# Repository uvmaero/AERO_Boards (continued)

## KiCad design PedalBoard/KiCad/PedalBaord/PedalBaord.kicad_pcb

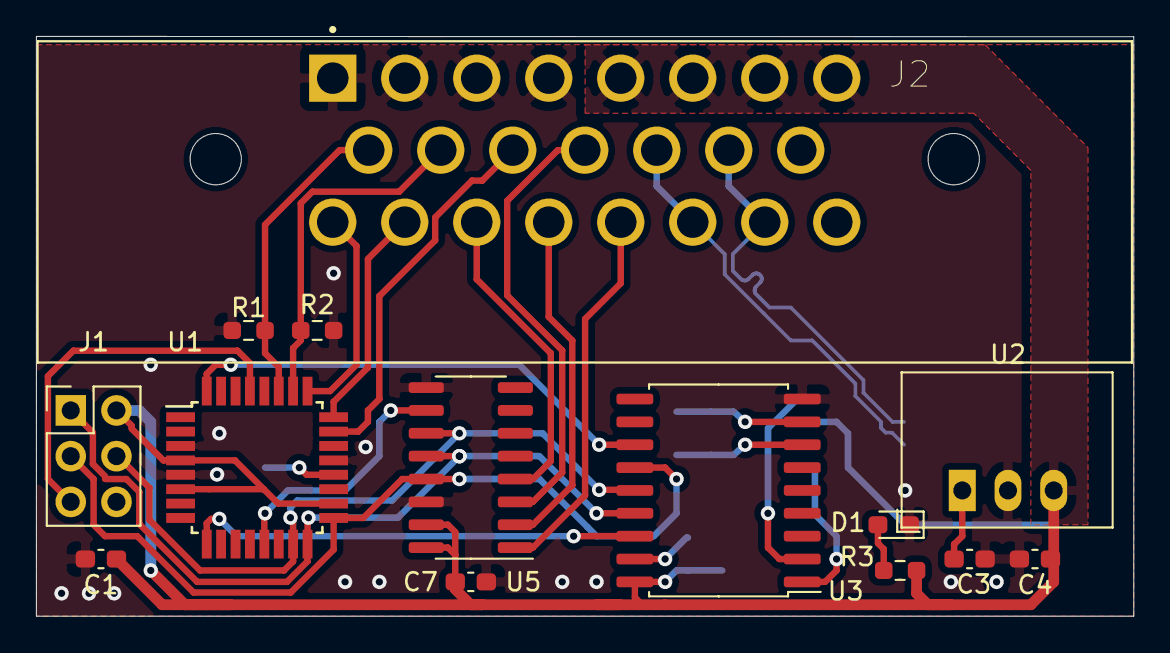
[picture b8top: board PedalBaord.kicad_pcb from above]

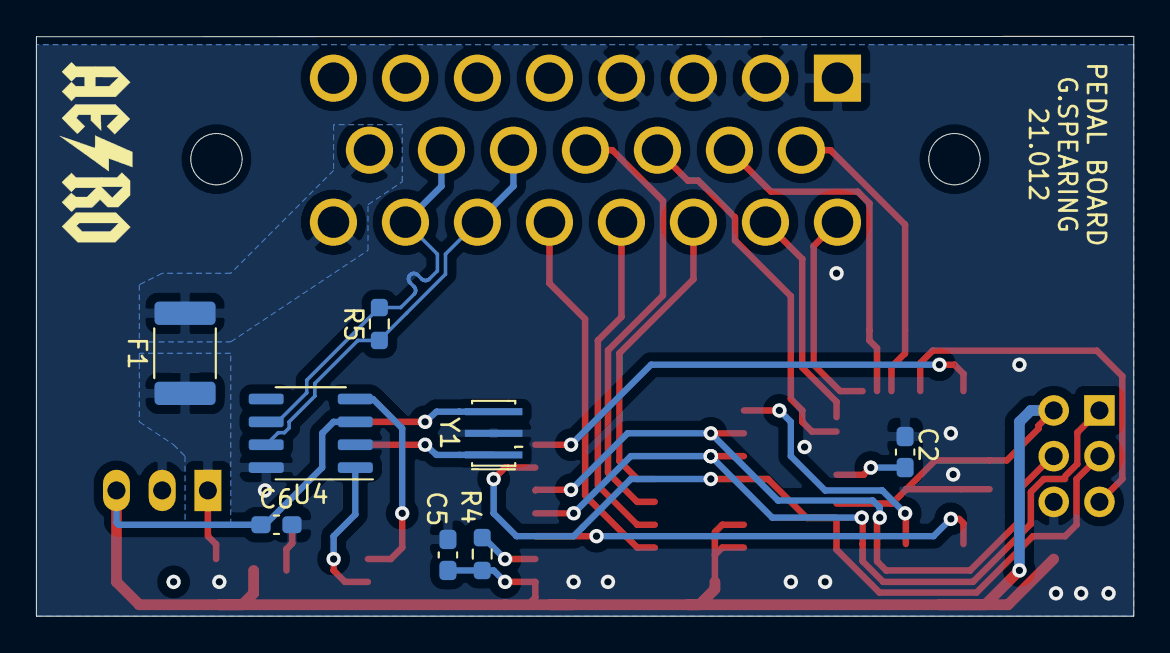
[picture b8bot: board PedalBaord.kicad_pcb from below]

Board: 2 copper layers, 61.0 x 32.2 mm, 22 parts (8 on the bottom side), 29 nets.

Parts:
C1, C2, C5, C6, C7: 0.1u; C_0603_1608Metric_Pad1.08x0.95mm_HandSolder
C3: 1u; C_0603_1608Metric_Pad1.08x0.95mm_HandSolder
C4: 10u; C_0603_1608Metric_Pad1.08x0.95mm_HandSolder
D1: LED; LED_0603_1608Metric_Pad1.05x0.95mm_HandSolder
F1: MF-MSMF050; Fuse_1812_4532Metric_Pad1.30x3.40mm_HandSolder
J1: Conn_02x03_Odd_Even; PinHeader_2x03_P2.54mm_Vertical
J2: Conn_01x23; TE_1-770669-1_23pin_Horizontal
R1, R2, R4: 10K; R_0603_1608Metric_Pad0.98x0.95mm_HandSolder
R3: 330; R_0603_1608Metric_Pad0.98x0.95mm_HandSolder
R5: 120; R_0603_1608Metric_Pad0.98x0.95mm_HandSolder
U1: ATmega328P-AU; TQFP-32_7x7mm_P0.8mm
U2: R-785.0-1.0; Converter_DCDC_RECOM_R-78E-0.5_THT
U3: MCP2515-xSO; SOIC-18W_7.5x11.6mm_P1.27mm
U4: MCP2551-I-SN; SOIC-8_3.9x4.9mm_P1.27mm
U5: MCP3008; SOIC-16_3.9x9.9mm_P1.27mm
Y1: 16MHz; Resonator_SMD_muRata_CSTxExxV-3Pin_3.0x1.1mm_HandSoldering

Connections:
+5V: C1.1, C4.1, C5.1, C6.1, C7.1, J1.2, J2.5, J2.6, J2.7, J2.8, R3.2, R4.1, U1.4, U1.6, U1.18, U2.3, U3.18, U4.3, U5.15, U5.16
+12V: F1.2, J2.15, J2.23
/ACC0: J2.9, R1.1, U1.27
/ACC1: J2.10, R2.1, U1.26
/ADC_CS: U1.13, U5.10
/BRAKE0: J2.16, U1.25
/BRAKE1: J2.17, U1.24
/CAN+: J2.13, J2.21, R5.1, U4.7
/CAN-: J2.14, J2.22, R5.2, U4.6
/CAN_CS: U1.9, U3.16
/CAN_INT: U1.32, U3.12
/DAMPER_L: J2.12, U5.3
/DAMPER_R: J2.18, U5.4
/MISO: J1.1, U1.16, U3.15, U5.12
/MOSI: J1.4, U1.15, U3.14, U5.11
/RESET: J1.5, U1.29
/RXCAN: U3.2, U4.4
/SCK: J1.3, U1.17, U3.13, U5.13
/STEER: J2.11, U1.23
/TXCAN: U3.1, U4.1
/WHEEL_L: J2.20, U5.1
/WHEEL_R: J2.19, U5.2
GND: C1.2, C2.2, C3.2, C4.2, C5.2, C6.2, C7.2, D1.1, J1.6, J2.1, J2.2, J2.3, J2.4, R1.2, R2.2, U1.3, U1.5, U1.21, U2.2, U3.9, U4.2, U4.8, U5.9, U5.14, Y1.2
unnamed: C2.1, U1.20
unnamed: C3.1, F1.1, U2.1
unnamed: D1.2, R3.1
unnamed: R4.2, U3.17
unnamed: U3.7, Y1.1
unnamed: U3.8, Y1.3

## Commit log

2021-03-18 Initial Commit Add Current Boards
2021-03-18 Re Organize Structure
2021-03-25 add parts note
